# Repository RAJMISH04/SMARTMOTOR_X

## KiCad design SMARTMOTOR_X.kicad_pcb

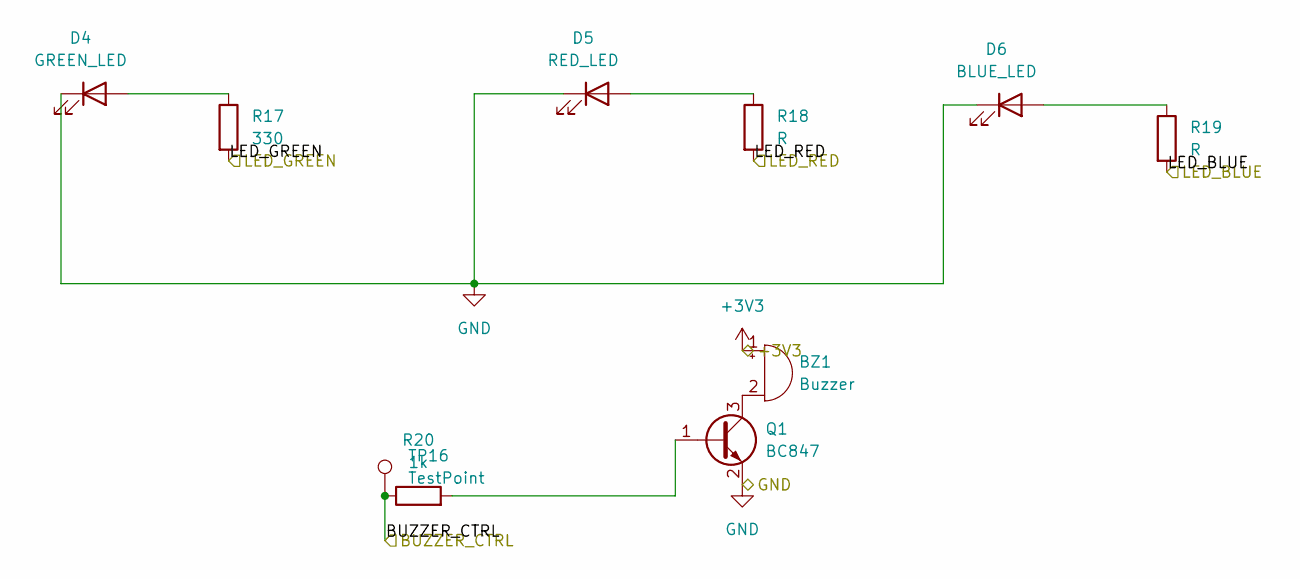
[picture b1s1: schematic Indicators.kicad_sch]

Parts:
BZ1: Buzzer; Buzzer_12x9.5RM7.6
D4: GREEN_LED; LED_0603_1608Metric
D5: RED_LED; LED_0603_1608Metric
D6: BLUE_LED; LED_0603_1608Metric
Q1: BC847; SOT-23
R17: 330; R_0603_1608Metric
R18, R19: R; R_0603_1608Metric
R20: 1k; R_0603_1608Metric
TP16: TestPoint; TestPoint_Pad_D1.5mm

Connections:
+3V3: BZ1.1 (+); also elsewhere on the board
BUZZER_CTRL: R20.1, TP16.1 (1_1); also elsewhere on the board
LED_BLUE: R19.2; also elsewhere on the board
LED_GREEN: R17.2; also elsewhere on the board
LED_RED: R18.2; also elsewhere on the board
unnamed: BZ1.2 (-), Q1.3 (C)
unnamed: D4.2 (A), R17.1
unnamed: D5.2 (A), R18.1
unnamed: D6.2 (A), R19.1
unnamed: Q1.1 (B), R20.2

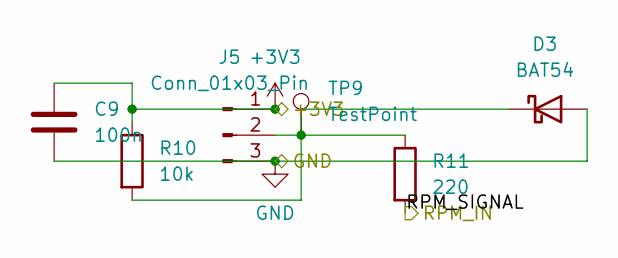
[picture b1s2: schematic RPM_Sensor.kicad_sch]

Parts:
C9: 100n; C_0603_1608Metric
D3: BAT54; SOT-23
J5: Conn_01x03_Pin; FanPinHeader_1x03_P2.54mm_Vertical
R10: 10k; R_0603_1608Metric
R11: 220; R_0603_1608Metric
TP9: TestPoint; TestPoint_Pad_D1.5mm

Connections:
+3V3: C9.1, J5.1, R10.1; also elsewhere on the board
unnamed: D3.1 (K), J5.2, R10.2, R11.1, TP9.1 (1_1)
RPM_IN: R11.2; also elsewhere on the board

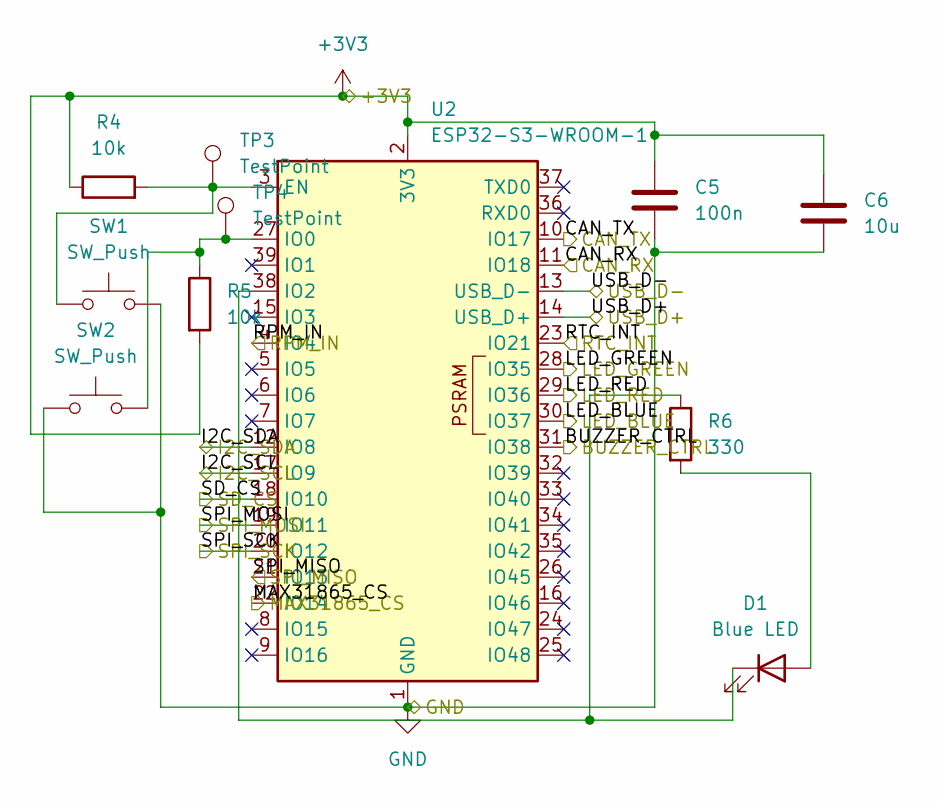
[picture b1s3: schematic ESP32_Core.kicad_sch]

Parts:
C5: 100n; C_0603_1608Metric
C6: 10u; C_0603_1608Metric
D1: Blue LED; LED_0603_1608Metric
R4, R5: 10k; R_0603_1608Metric
R6: 330; R_0603_1608Metric
SW1, SW2: SW_Push; SW_SPST_TL3342
TP3, TP4: TestPoint; TestPoint_Pad_D1.5mm
U2: ESP32-S3-WROOM-1

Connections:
+3V3: C5.1, C6.1, R4.1, R5.2, U2.2 (3V3); also elsewhere on the board
BUZZER_CTRL: U2.31 (IO38); also elsewhere on the board
CAN_RX: U2.11 (IO18); also elsewhere on the board
CAN_TX: U2.10 (IO17); also elsewhere on the board
I2C_SCL: U2.17 (IO9); also elsewhere on the board
I2C_SDA: U2.12 (IO8); also elsewhere on the board
LED_BLUE: U2.30 (IO37); also elsewhere on the board
LED_GREEN: U2.28 (IO35); also elsewhere on the board
LED_RED: U2.29 (IO36); also elsewhere on the board
MAX31865_CS: U2.22 (IO14); also elsewhere on the board
unnamed: D1.2 (A), R6.2
unnamed: D1.1 (K), R6.1, U2.38 (IO2)
unnamed: R4.2, SW1.1, TP3.1 (1_1), U2.3 (EN)
unnamed: R5.1, SW2.2, TP4.1 (1_1), U2.27 (IO0)
RPM_IN: U2.4 (IO4); also elsewhere on the board
RTC_INT: U2.23 (IO21); also elsewhere on the board
SD_CS: U2.18 (IO10); also elsewhere on the board
SPI_MISO: U2.21 (IO13); also elsewhere on the board
SPI_SCK: U2.20 (IO12); also elsewhere on the board
USB_D+: U2.14 (USB_D+); also elsewhere on the board

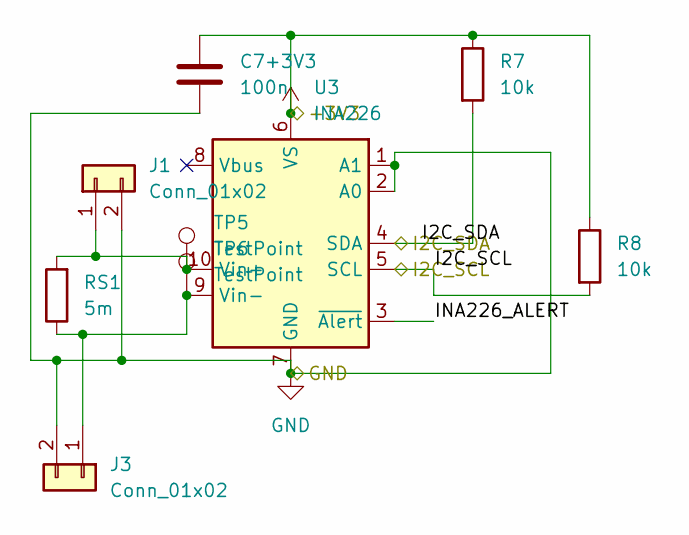
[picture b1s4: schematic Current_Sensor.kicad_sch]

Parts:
C7: 100n; C_0603_1608Metric
J1, J3: Conn_01x02; PinHeader_1x02_P2.54mm_Vertical
R7, R8: 10k; R_0603_1608Metric
RS1: 5m; R_2512_6332Metric
TP5, TP6: TestPoint; TestPoint_Pad_D1.5mm
U3: INA226; TSSOP-10_3x3mm_P0.5mm

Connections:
+3V3: C7.1, R7.1, R8.1, U3.6 (VS); also elsewhere on the board
/Current_Sensor/INA226_ALERT: U3.3 (~Alert)
I2C_SCL: R8.2, U3.5 (SCL); also elsewhere on the board
I2C_SDA: R7.2, U3.4 (SDA); also elsewhere on the board
unnamed: J1.1, RS1.2, TP5.1 (1_1), U3.10 (Vin+)
unnamed: J3.1, RS1.1, TP6.1 (1_1), U3.9 (Vin-)

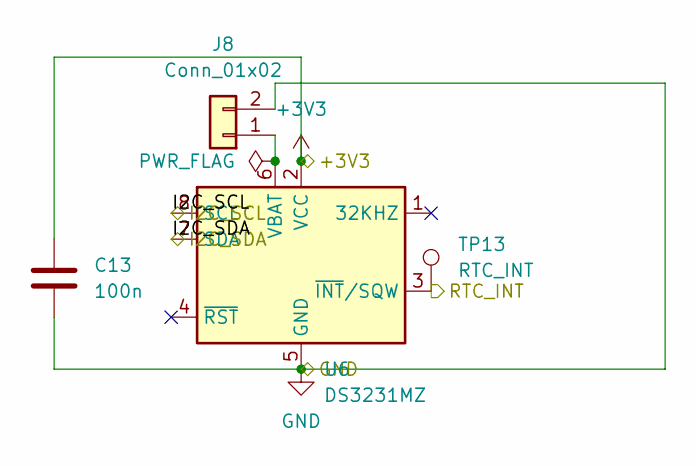
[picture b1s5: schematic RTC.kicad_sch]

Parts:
C13: 100n; C_0603_1608Metric
J8: Conn_01x02; PinHeader_1x02_P2.54mm_Vertical
TP13: RTC_INT; TestPoint_Pad_D1.5mm
U6: DS3231MZ; SOIC-8_3.9x4.9mm_P1.27mm

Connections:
+3V3: C13.1, U6.2 (VCC); also elsewhere on the board
I2C_SCL: U6.8 (SCL); also elsewhere on the board
I2C_SDA: U6.7 (SDA); also elsewhere on the board
unnamed: J8.1, U6.6 (VBAT)
RTC_INT: TP13.1 (1_1), U6.3 (~INT/SQW); also elsewhere on the board

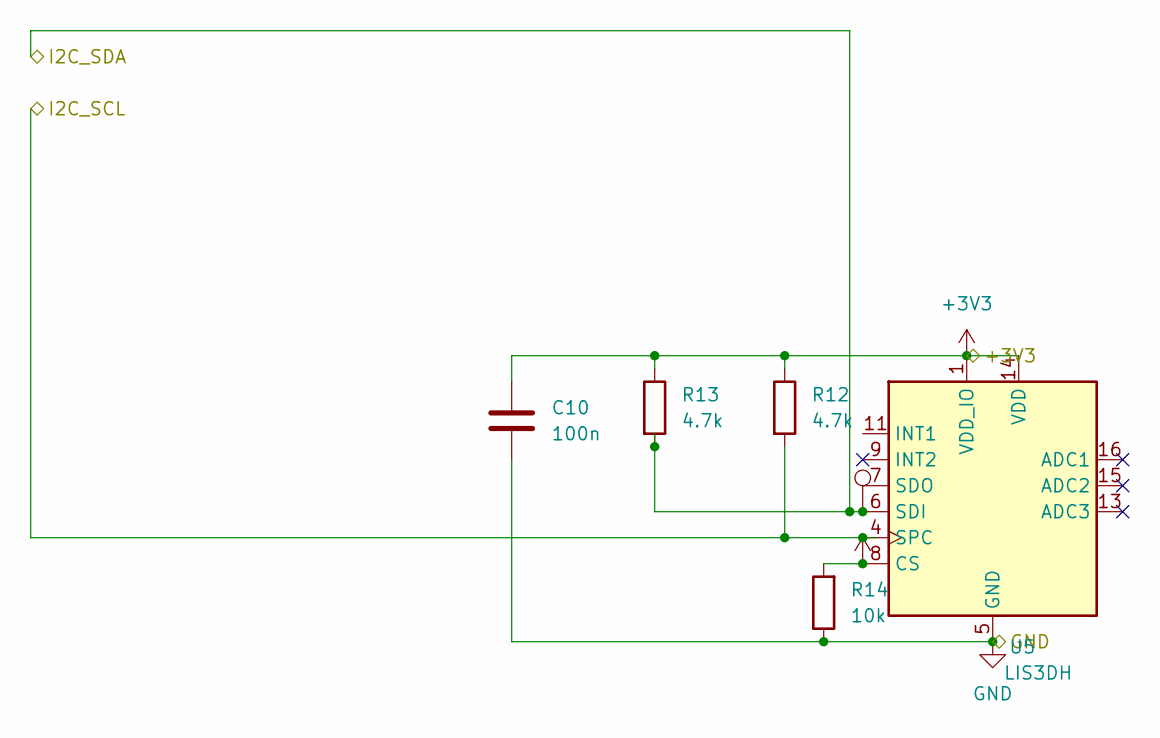
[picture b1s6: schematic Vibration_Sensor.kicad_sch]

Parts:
C10: 100n; C_0603_1608Metric
R12, R13: 4.7k; R_0603_1608Metric
R14: 10k; R_0603_1608Metric
TP10: TestPoint; TestPoint_Pad_D1.5mm
U5: LIS3DH; LGA-16_3x3mm_P0.5mm_LayoutBorder3x5y

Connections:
+3V3: C10.1, R12.1, R13.1, R14.2, U5.1 (VDD_IO), U5.8 (CS), U5.14 (VDD); also elsewhere on the board
I2C_SCL: R12.2, U5.4 (SPC); also elsewhere on the board
I2C_SDA: R13.2, TP10.1 (1_1), U5.6 (SDI); also elsewhere on the board

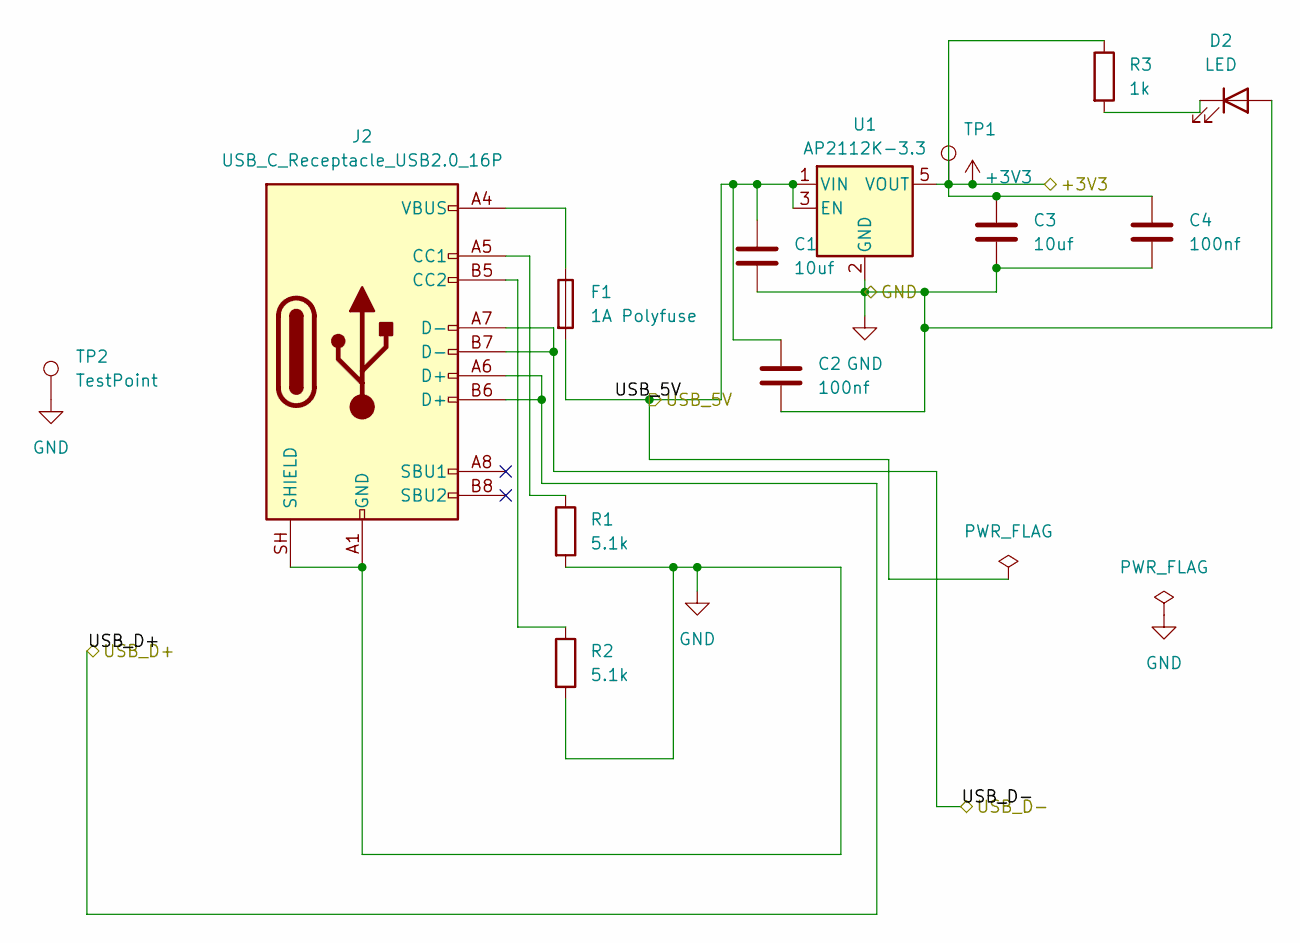
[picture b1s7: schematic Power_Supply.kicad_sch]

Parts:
C1, C3: 10uf; C_0603_1608Metric
C2, C4: 100nf; C_0603_1608Metric
D2: LED; LED_0603_1608Metric
F1: 1A Polyfuse; Fuse_1206_3216Metric
J2: USB_C_Receptacle_USB2.0_16P; USB_C_Receptacle_GCT_USB4105-xx-A_16P_TopMnt_Horizontal
R1, R2: 5.1k; R_0603_1608Metric
R3: 1k; R_0603_1608Metric
TP1, TP2: TestPoint; TestPoint_Pad_D1.5mm
U1: AP2112K-3.3; SOT-23-5

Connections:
+3V3: C3.1, C4.1, R3.1, TP1.1 (1_1), U1.5 (VOUT); also elsewhere on the board
unnamed: F1.1, J2.A4 (VBUS), J2.A9 (VBUS), J2.B4 (VBUS), J2.B9 (VBUS)
unnamed: J2.A5 (CC1), R1.1
unnamed: J2.B5 (CC2), R2.1
USB_5V: C1.1, C2.1, F1.2, U1.1 (VIN), U1.3 (EN)
USB_D+: J2.A6 (D+), J2.B6 (D+); also elsewhere on the board
USB_D-: J2.A7 (D-), J2.B7 (D-)

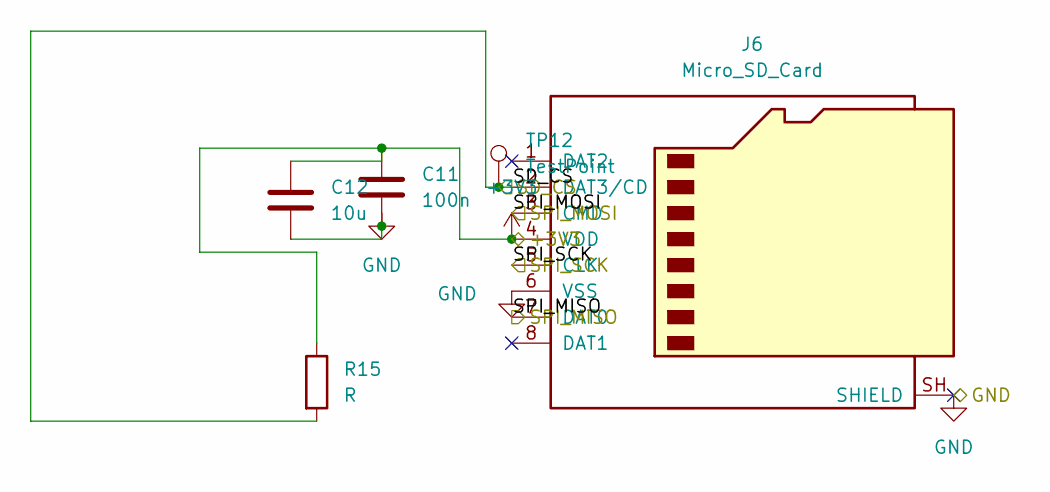
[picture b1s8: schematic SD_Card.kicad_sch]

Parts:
C11: 100n; C_0603_1608Metric
C12: 10u; C_0603_1608Metric
J6: Micro_SD_Card; microSD_HC_Molex_104031-0811
R15: R; R_0603_1608Metric
TP12: TestPoint; TestPoint_Pad_D1.5mm

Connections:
+3V3: C11.1, C12.1, J6.4 (VDD), R15.1; also elsewhere on the board
SD_CS: J6.2 (DAT3/CD), R15.2, TP12.1 (1_1); also elsewhere on the board
SPI_MISO: J6.7 (DAT0); also elsewhere on the board
SPI_MOSI: J6.3 (CMD); also elsewhere on the board
SPI_SCK: J6.5 (CLK); also elsewhere on the board

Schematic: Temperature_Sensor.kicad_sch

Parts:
C8: 100n; C_0603_1608Metric
J4: Conn_01x04; FanPinHeader_1x04_P2.54mm_Vertical
R9: 430; R_0603_1608Metric
TP7, TP8: TestPoint; TestPoint_Pad_D1.5mm
U4: MAX31865xAP; SSOP-20_5.3x7.2mm_P0.65mm

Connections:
+3V3: C8.1, U4.3 (VDD); also elsewhere on the board
MAX31865_CS: U4.16 (~CS); also elsewhere on the board
unnamed: J4.1, R9.2, U4.8 (FORCE+)
unnamed: J4.2, TP7.1 (1_1), U4.10 (RTDIN+)
unnamed: J4.3, TP8.1 (1_1), U4.11 (RTDIN-)
unnamed: J4.4, U4.12 (FORCE-)
unnamed: R9.1, U4.5 (REFIN+)
SPI_MISO: U4.17 (SDO); also elsewhere on the board
SPI_MOSI: U4.14 (SDI); also elsewhere on the board
SPI_SCK: U4.15 (SCLK); also elsewhere on the board

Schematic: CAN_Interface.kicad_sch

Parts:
C14: 100n; C_0603_1608Metric
C15: 10u; C_0603_1608Metric
J7: Conn_01x02; PinHeader_1x02_P2.54mm_Vertical
JP1: SolderJumper_2_Open; SolderJumper-2_P1.3mm_Open_RoundedPad1.0x1.5mm
R16: 120; R_0603_1608Metric
TP14, TP15: TestPoint; TestPoint_Pad_D1.5mm
U7: SN65HVD230; SOIC-8_3.9x4.9mm_P1.27mm

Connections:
+3V3: C14.1, C15.1, U7.3 (VCC); also elsewhere on the board
/CAN_Interface/CANH bus: J7.1, JP1.1 (A), TP14.1 (1_1), U7.7 (CANH)
/CAN_Interface/CANL bus: J7.2, TP15.1 (1_1), U7.6 (CANL)
CAN_RX: U7.4 (R); also elsewhere on the board
CAN_TX: U7.1 (D); also elsewhere on the board
unnamed: JP1.2 (B), R16.1

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
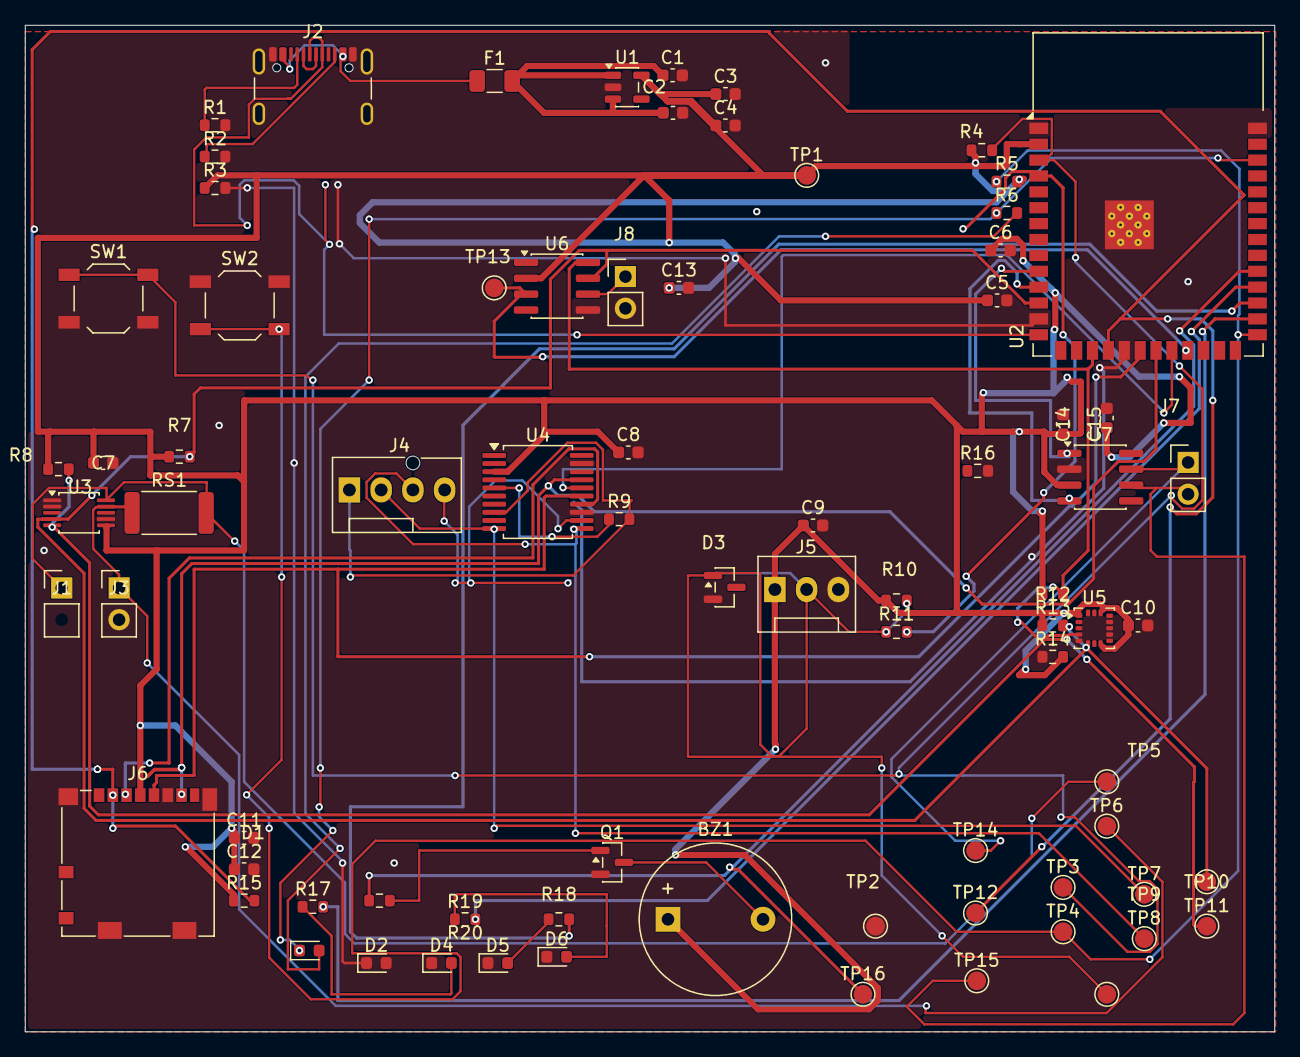
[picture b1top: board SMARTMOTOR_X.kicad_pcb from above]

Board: 2 copper layers, 99.9 x 80.5 mm, 78 parts (0 on the bottom side), 43 nets.

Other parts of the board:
TP11: TestPoint; TestPoint_Pad_D1.5mm

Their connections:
I2C_SCL: TP11.1 (1_1); also elsewhere on the board
